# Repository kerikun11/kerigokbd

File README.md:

# KERIgoKBD (KERI's Ergonomic Keyboard)

けりの自作キーボードの設計データ。

```tree
kerigokbd/
├── hardware/
│   ├── kerigokbd/      # KERIgoKBD common PCB/case parts
│   └── README.md       # Hardware parts and compatibility table
├── software/
│   └── qmk/
│       ├── firmware/   # QMK Firmware for VIA (git submodule)
│       ├── keyboards/  # Keyboard entries for QMK Firmware
│       ├── qmk.sh      # build script
│       └── README.md   # build manual
├── .gitmodules
└── README.md
```

## 作品一覧

ハードウェア部品とファームウェアの対応は [`hardware/README.md`](./hardware/README.md) に記載。

| 作品                                                 | コメント                                                            |
| :--------------------------------------------------- | :------------------------------------------------------------------ |
| [KERIgoKBD v1](./hardware/kerigokbd/kerigokbd_v1/)   | はじめての自作エルゴノミックキーボード。                            |
| [KERIgoKBD v2](./hardware/kerigokbd/kerigokbd_v2/)   | KERIgoKBD v1 にトラックパッドを追加した構成。                       |
| [KERIgoKBD Corne v4](./hardware/kerigokbd_corne_v4/) | Corne V4 Chocolate のケースとファームウェアをカスタマイズしたもの。 |
| Keyball44 RP2040                                     | Keyball44 のマイコンボードを RP2040 Pro Micro に差し替えたもの。    |

## KERIgoKBD v1

[けり](https://github.com/kerikun11)のはじめての自作キーボード。

## KERIgoKBD v2

KERIgoKBD v1 の右手側にトラックパッドを追加した構成。

## KERIgoKBD Corne v4

[foostan](https://github.com/foostan)さんの[Corne V4 Chocolate](https://github.com/foostan/crkbd)のケースとファームウェアをカスタマイズしたもの。

## Keyball44 RP2040

[Yowkees](https://github.com/Yowkees)さんの[Keyball44](https://github.com/Yowkees/keyball)のマイコンボードを `RP2040 Pro Micro` に差し替えたもの。

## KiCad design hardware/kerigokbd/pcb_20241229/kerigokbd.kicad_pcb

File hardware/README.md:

# Hardware

KERIgoKBD のハードウェア設計データ。ここでは PCB、ケースなどの物理パーツを作品ごとに分離して管理する。

## 対応表

| 作品                                      | PCB                                         | ケース                                                          | ファームウェア                                                     | メモ                     |
| :---------------------------------------- | :------------------------------------------ | :-------------------------------------------------------------- | :----------------------------------------------------------------- | :----------------------- |
| [KERIgoKBD v1](./kerigokbd/kerigokbd_v1/) | [`pcb_20260222`](./kerigokbd/pcb_20260222/) | [`case_20260222`](./kerigokbd/case_20260222/)                   | [`kerigokbd_v1`](../software/qmk/keyboards/kerigokbd/kerigokbd_v1) | 標準構成                 |
| [KERIgoKBD v2](./kerigokbd/kerigokbd_v2/) | [`pcb_20260222`](./kerigokbd/pcb_20260222/) | [`case_20260222_trackpad`](./kerigokbd/case_20260222_trackpad/) | [`kerigokbd_v2`](../software/qmk/keyboards/kerigokbd/kerigokbd_v2) | 右手にトラックパッド追加 |

## KERIgoKBD パーツ

### PCB

| パーツ                                      | 内容                                   |
| :------------------------------------------ | :------------------------------------- |
| [`pcb_20241229`](./kerigokbd/pcb_20241229/) | v1.0 初版。I2Cピンアサインにミスあり。 |
| [`pcb_20250208`](./kerigokbd/pcb_20250208/) | v1.1 I2Cピンアサイン修正版。           |
| [`pcb_20260222`](./kerigokbd/pcb_20260222/) | v1.2 小型版。v1/v2 共通 PCB。          |

### ケース

| パーツ                                                          | 内容                                      |
| :-------------------------------------------------------------- | :---------------------------------------- |
| [`case_20250208`](./kerigokbd/case_20250208/)                   | PCB v1.0 と v1.1 向けのケース。           |
| [`case_20260222`](./kerigokbd/case_20260222/)                   | PCB v1.2 向けケース。                     |
| [`case_20260222_trackpad`](./kerigokbd/case_20260222_trackpad/) | PCB v1.2 向け、トラックパッド対応ケース。 |

## その他

- [`kerigokbd_corne_v4`](./kerigokbd_corne_v4/) は Corne V4 Chocolate のカスタムケース。

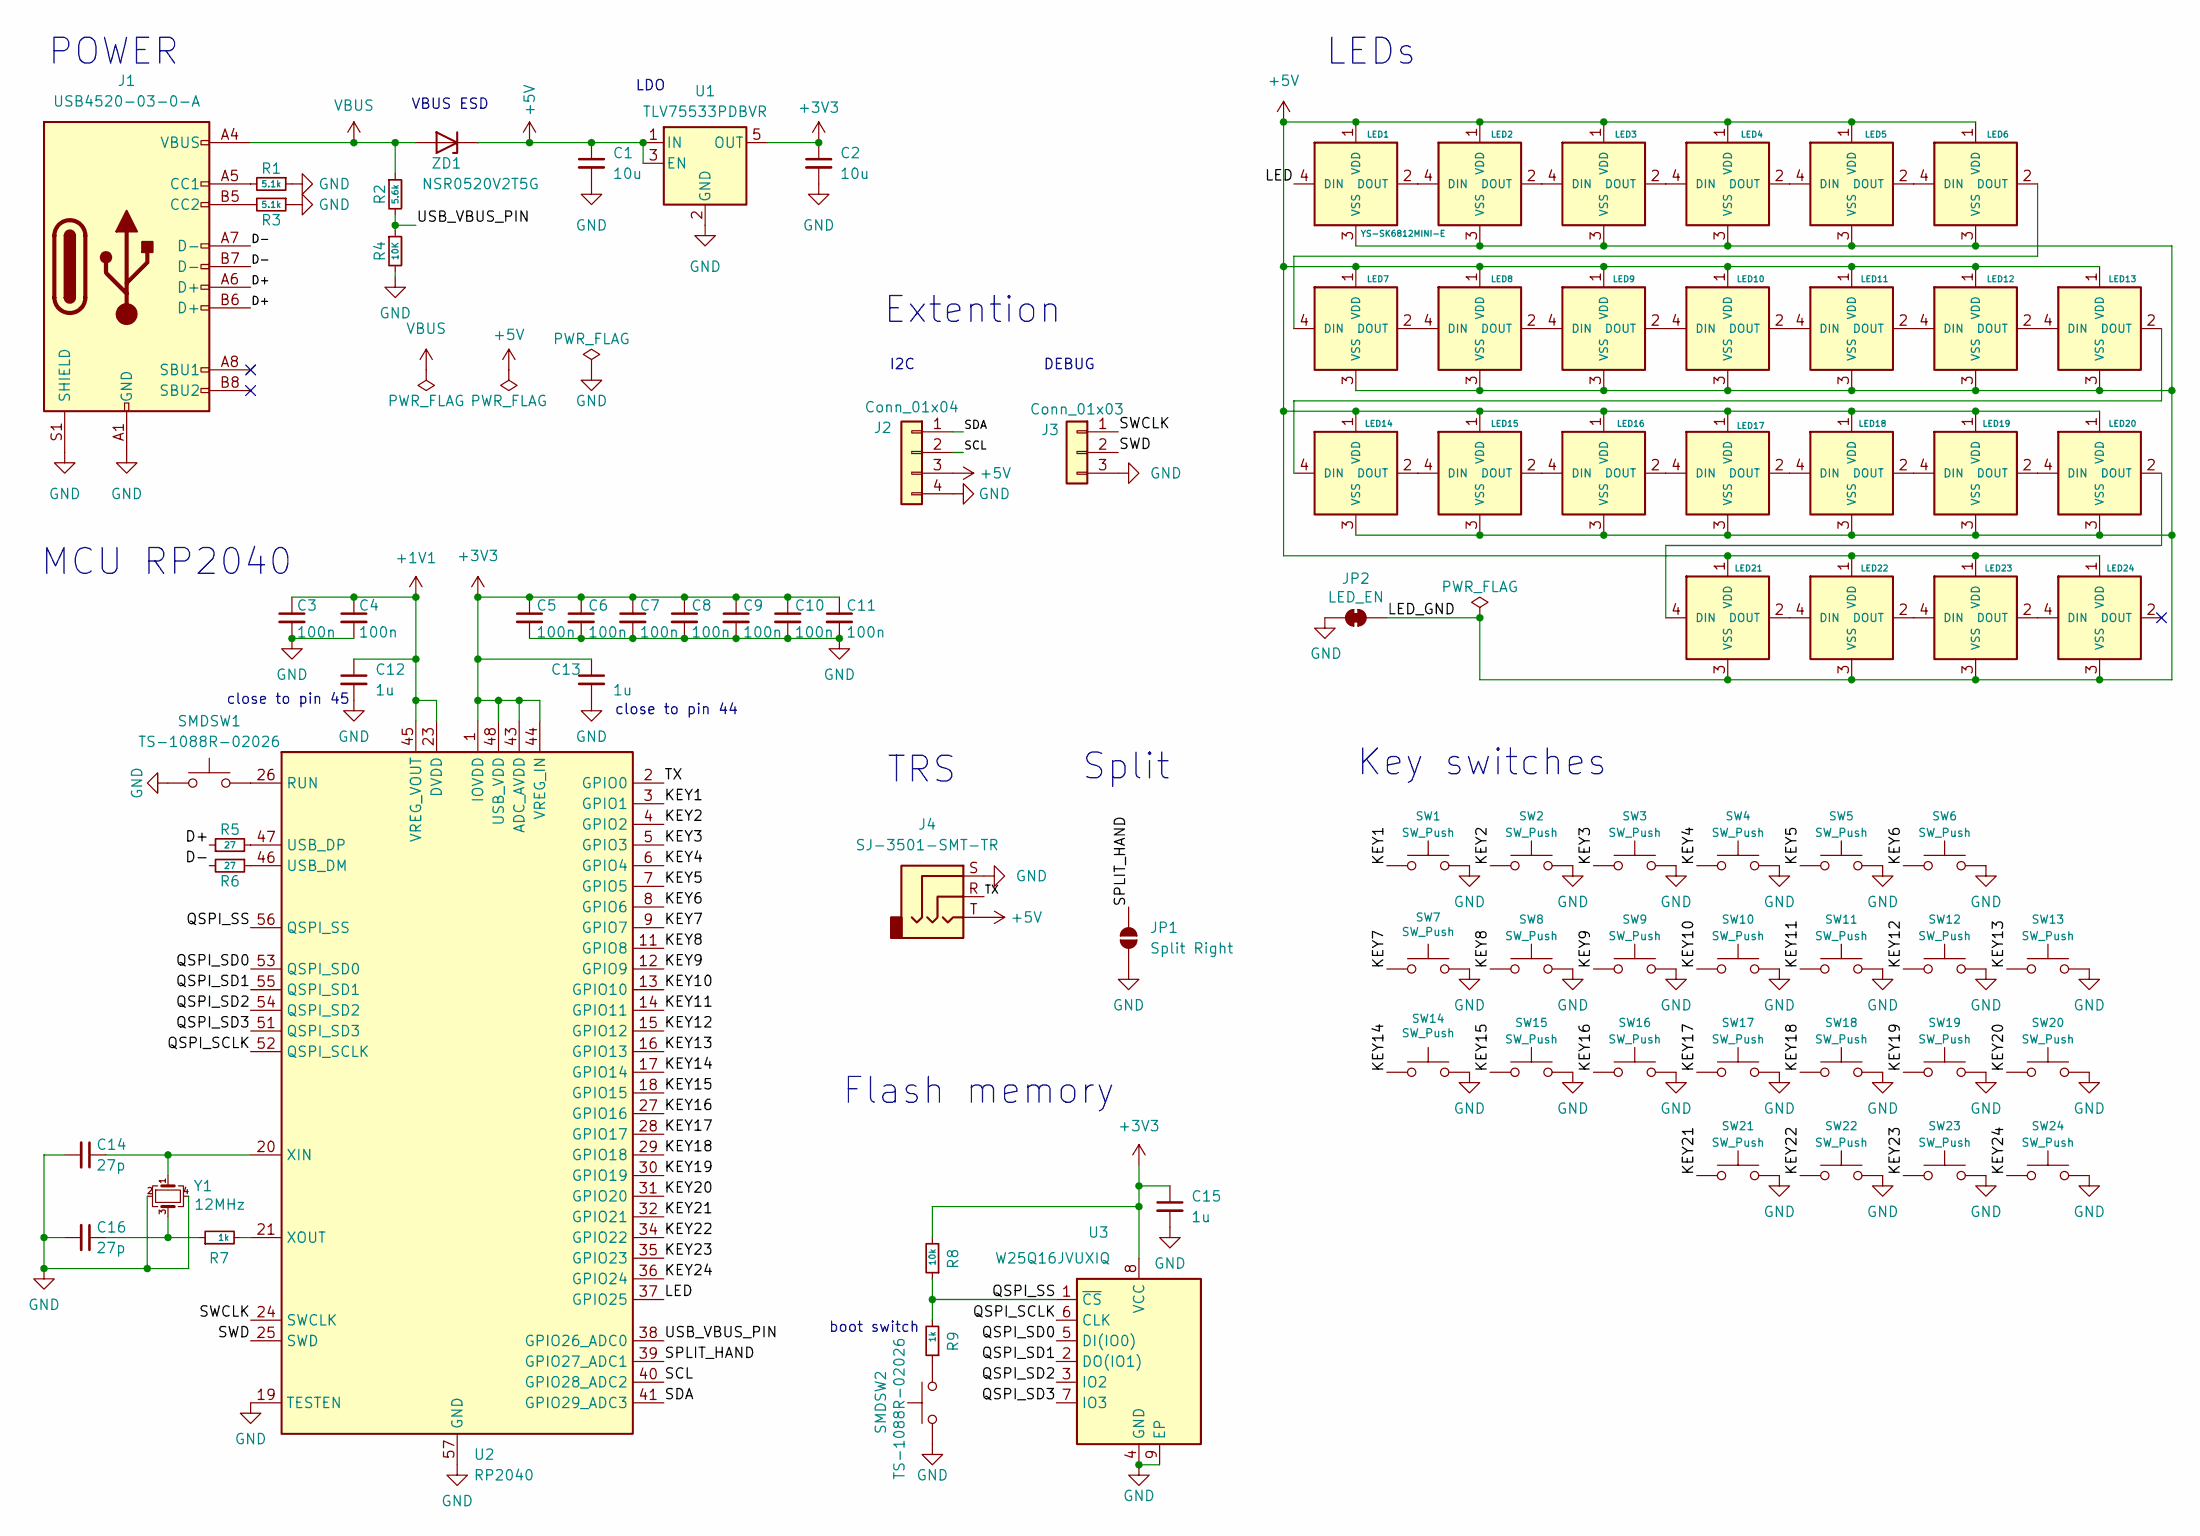
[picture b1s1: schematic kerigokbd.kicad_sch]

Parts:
C1, C2: 10u; C_0402_1005Metric
C3, C4, C5, C6, C7, C8, C9, C10, C11: 100n; C_0402_1005Metric
C12, C13, C15: 1u; C_0402_1005Metric
C14, C16: 27p; C_0402_1005Metric
J1: USB4520-03-0-A; TYPE-C-31-M-13C-dual; JLCPCB Part # C2848620
J2: Conn_01x04; PinHeader_1x04_P1.27mm_Vertical
J3: Conn_01x03; PinHeader_1x03_P1.27mm_Vertical
J4: SJ-3501-SMT-TR; PJ-398A-5A_PJ-399B-6A-dual; JLCPCB Part # C128994
JP1: Split Right; SolderJumper-2_P1.3mm_Open_TrianglePad1.0x1.5mm
JP2: LED_EN; SolderJumper-2_P1.3mm_Bridged_RoundedPad1.0x1.5mm
LED1, LED2, LED3, LED4, LED5, LED6, LED7, LED8, LED9, LED10, LED11, LED12, LED13, LED14, LED15, LED16, LED17, LED18, LED19, LED20, LED21, LED22, LED23, LED24: YS-SK6812MINI-E; YS-SK6812MINI-E-dual
R1, R3: 5.1k; R_0402_1005Metric
R2: 5.6k; R_0402_1005Metric
R4: 10K; R_0402_1005Metric
R5, R6: 27; R_0402_1005Metric
R7, R9: 1k; R_0402_1005Metric
R8: 10k; R_0402_1005Metric
SMDSW1, SMDSW2: TS-1088R-02026; PinHeader_1x02_P1.27mm_Vertical; JLCPCB Part # C455280
SW1, SW2, SW3, SW4, SW5, SW6, SW7, SW8, SW9, SW10, SW11, SW12, SW13, SW14, SW15, SW16, SW17, SW18, SW19, SW20, SW21, SW22, SW23, SW24: SW_Push; keyswitch_choc12_hotswap_1u_dual
U1: TLV75533PDBVR; SOT-23-5
U2: RP2040; QFN-56-1EP_7x7mm_P0.4mm_EP3.2x3.2mm; JLCPCB Part # C2040
U3: W25Q16JVUXIQ; Winbond_USON-8-1EP_3x2mm_P0.5mm_EP0.2x1.6mm; JLCPCB Part # C113767
Y1: 12MHz; Crystal_SMD_3225-4Pin_3.2x2.5mm; MFR.Part # Q22FA23V0041800; JLCPCB Part # C91749
ZD1: NSR0520V2T5G; D_SOD-523; JLCPCB Part # C145179

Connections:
+1V1: C3.1, C4.1, C12.1, U2.23 (DVDD), U2.45 (VREG_VOUT), U2.50 (DVDD)
+3V3: C2.1, C5.1, C6.1, C7.1, C8.1, C9.1, C10.1, C11.1, C13.1, C15.1, R8.2, U1.5 (OUT), U2.1 (IOVDD), U2.10 (IOVDD), U2.22 (IOVDD), U2.33 (IOVDD), U2.42 (IOVDD), U2.43 (ADC_AVDD), U2.44 (VREG_IN), U2.48 (USB_VDD), U2.49 (IOVDD), U3.8 (VCC)
+5V: C1.1, J2.3, J4.T, LED1.1 (VDD), LED2.1 (VDD), LED3.1 (VDD), LED4.1 (VDD), LED5.1 (VDD), LED6.1 (VDD), LED7.1 (VDD), LED8.1 (VDD), LED9.1 (VDD), LED10.1 (VDD), LED11.1 (VDD), LED12.1 (VDD), LED13.1 (VDD), LED14.1 (VDD), LED15.1 (VDD), LED16.1 (VDD), LED17.1 (VDD), LED18.1 (VDD), LED19.1 (VDD), LED20.1 (VDD), LED21.1 (VDD), LED22.1 (VDD), LED23.1 (VDD), LED24.1 (VDD), U1.1 (IN), U1.3 (EN), ZD1.1 (K)
/D+: J1.A6 (D+), J1.B6 (D+), R5.1
/D-: J1.A7 (D-), J1.B7 (D-), R6.2
/KEY1: SW1.1, U2.3 (GPIO1)
/KEY2: SW2.1, U2.4 (GPIO2)
/KEY3: SW3.1, U2.5 (GPIO3)
/KEY4: SW4.1, U2.6 (GPIO4)
/KEY5: SW5.1, U2.7 (GPIO5)
/KEY6: SW6.1, U2.8 (GPIO6)
/KEY7: SW7.1, U2.9 (GPIO7)
/KEY8: SW8.1, U2.11 (GPIO8)
/KEY9: SW9.1, U2.12 (GPIO9)
/KEY10: SW10.1, U2.13 (GPIO10)
/KEY11: SW11.1, U2.14 (GPIO11)
/KEY12: SW12.1, U2.15 (GPIO12)
/KEY13: SW13.1, U2.16 (GPIO13)
/KEY14: SW14.1, U2.17 (GPIO14)
/KEY15: SW15.1, U2.18 (GPIO15)
/KEY16: SW16.1, U2.27 (GPIO16)
/KEY17: SW17.1, U2.28 (GPIO17)
/KEY18: SW18.1, U2.29 (GPIO18)
/KEY19: SW19.1, U2.30 (GPIO19)
/KEY20: SW20.1, U2.31 (GPIO20)
/KEY21: SW21.1, U2.32 (GPIO21)
/KEY22: SW22.1, U2.34 (GPIO22)
/KEY23: SW23.1, U2.35 (GPIO23)
/KEY24: SW24.1, U2.36 (GPIO24)
/LED: LED1.4 (DIN), U2.37 (GPIO25)
/LED_GND: JP2.2 (B), LED1.3 (VSS), LED2.3 (VSS), LED3.3 (VSS), LED4.3 (VSS), LED5.3 (VSS), LED6.3 (VSS), LED7.3 (VSS), LED8.3 (VSS), LED9.3 (VSS), LED10.3 (VSS), LED11.3 (VSS), LED12.3 (VSS), LED13.3 (VSS), LED14.3 (VSS), LED15.3 (VSS), LED16.3 (VSS), LED17.3 (VSS), LED18.3 (VSS), LED19.3 (VSS), LED20.3 (VSS), LED21.3 (VSS), LED22.3 (VSS), LED23.3 (VSS), LED24.3 (VSS)
/QSPI_SCLK: U2.52 (QSPI_SCLK), U3.6 (CLK)
/QSPI_SD0: U2.53 (QSPI_SD0), U3.5 (DI(IO0))
/QSPI_SD1: U2.55 (QSPI_SD1), U3.2 (DO(IO1))
/QSPI_SD2: U2.54 (QSPI_SD2), U3.3 (IO2)
/QSPI_SD3: U2.51 (QSPI_SD3), U3.7 (IO3)
/QSPI_SS: R8.1, R9.2, U2.56 (QSPI_SS), U3.1 (~CS)
/SCL: J2.2, U2.40 (GPIO28_ADC2)
/SDA: J2.1, U2.41 (GPIO29_ADC3)
/SPLIT_HAND: JP1.2 (B), U2.39 (GPIO27_ADC1)
/SWCLK: J3.1, U2.24 (SWCLK)
/SWD: J3.2, U2.25 (SWD)
/TX: J4.R, U2.2 (GPIO0)
/USB_VBUS_PIN: R2.2, R4.1, U2.38 (GPIO26_ADC0)
GND: C1.2, C2.2, C3.2, C4.2, C5.2, C6.2, C7.2, C8.2, C9.2, C10.2, C11.2, C12.2, C13.2, C14.2, C15.2, C16.2, J1.A1 (GND), J1.A12 (GND), J1.B1 (GND), J1.B12 (GND), J1.S1 (SHIELD), J2.4, J3.3, J4.S, JP1.1 (A), JP2.1 (A), R1.1, R3.1, R4.2, SMDSW1.1, SMDSW2.1, SW1.2, SW2.2, SW3.2, SW4.2, SW5.2, SW6.2, SW7.2, SW8.2, SW9.2, SW10.2, SW11.2, SW12.2, SW13.2, SW14.2, SW15.2, SW16.2, SW17.2, SW18.2, SW19.2, SW20.2, SW21.2, SW22.2, SW23.2, SW24.2, U1.2 (GND), U2.19 (TESTEN), U2.57 (GND), U3.4 (GND), U3.9 (EP), Y1.2, Y1.4
unnamed: C16.1, R7.1, Y1.3
unnamed: J1.A5 (CC1), R1.2
unnamed: J1.B5 (CC2), R3.2
unnamed: LED1.2 (DOUT), LED2.4 (DIN)
unnamed: LED2.2 (DOUT), LED3.4 (DIN)
unnamed: LED3.2 (DOUT), LED4.4 (DIN)
unnamed: LED4.2 (DOUT), LED5.4 (DIN)
unnamed: LED5.2 (DOUT), LED6.4 (DIN)
unnamed: LED6.2 (DOUT), LED7.4 (DIN)
unnamed: LED7.2 (DOUT), LED8.4 (DIN)
unnamed: LED8.2 (DOUT), LED9.4 (DIN)
unnamed: LED9.2 (DOUT), LED10.4 (DIN)
unnamed: LED10.2 (DOUT), LED11.4 (DIN)
unnamed: LED11.2 (DOUT), LED12.4 (DIN)
unnamed: LED12.2 (DOUT), LED13.4 (DIN)
unnamed: LED13.2 (DOUT), LED14.4 (DIN)
unnamed: LED14.2 (DOUT), LED15.4 (DIN)
unnamed: LED15.2 (DOUT), LED16.4 (DIN)
unnamed: LED16.2 (DOUT), LED17.4 (DIN)
unnamed: LED17.2 (DOUT), LED18.4 (DIN)
unnamed: LED18.2 (DOUT), LED19.4 (DIN)
unnamed: LED19.2 (DOUT), LED20.4 (DIN)
unnamed: LED20.2 (DOUT), LED21.4 (DIN)
unnamed: LED21.2 (DOUT), LED22.4 (DIN)
unnamed: LED22.2 (DOUT), LED23.4 (DIN)
unnamed: LED23.2 (DOUT), LED24.4 (DIN)
unnamed: R9.1, SMDSW2.2
unnamed: SMDSW1.2, U2.26 (RUN)
unnamed: R6.1, U2.46 (USB_DM)
unnamed: R5.2, U2.47 (USB_DP)
unnamed: C14.1, U2.20 (XIN), Y1.1
unnamed: R7.2, U2.21 (XOUT)
VBUS: J1.A4 (VBUS), J1.A9 (VBUS), J1.B4 (VBUS), J1.B9 (VBUS), R2.1, ZD1.2 (A)

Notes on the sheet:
Key switches
Extention
LDO
POWER
close to pin 45
Split
VBUS ESD
I2C
boot switch
TRS
LEDs
close to pin 44
Flash memory
MCU RP2040
DEBUG

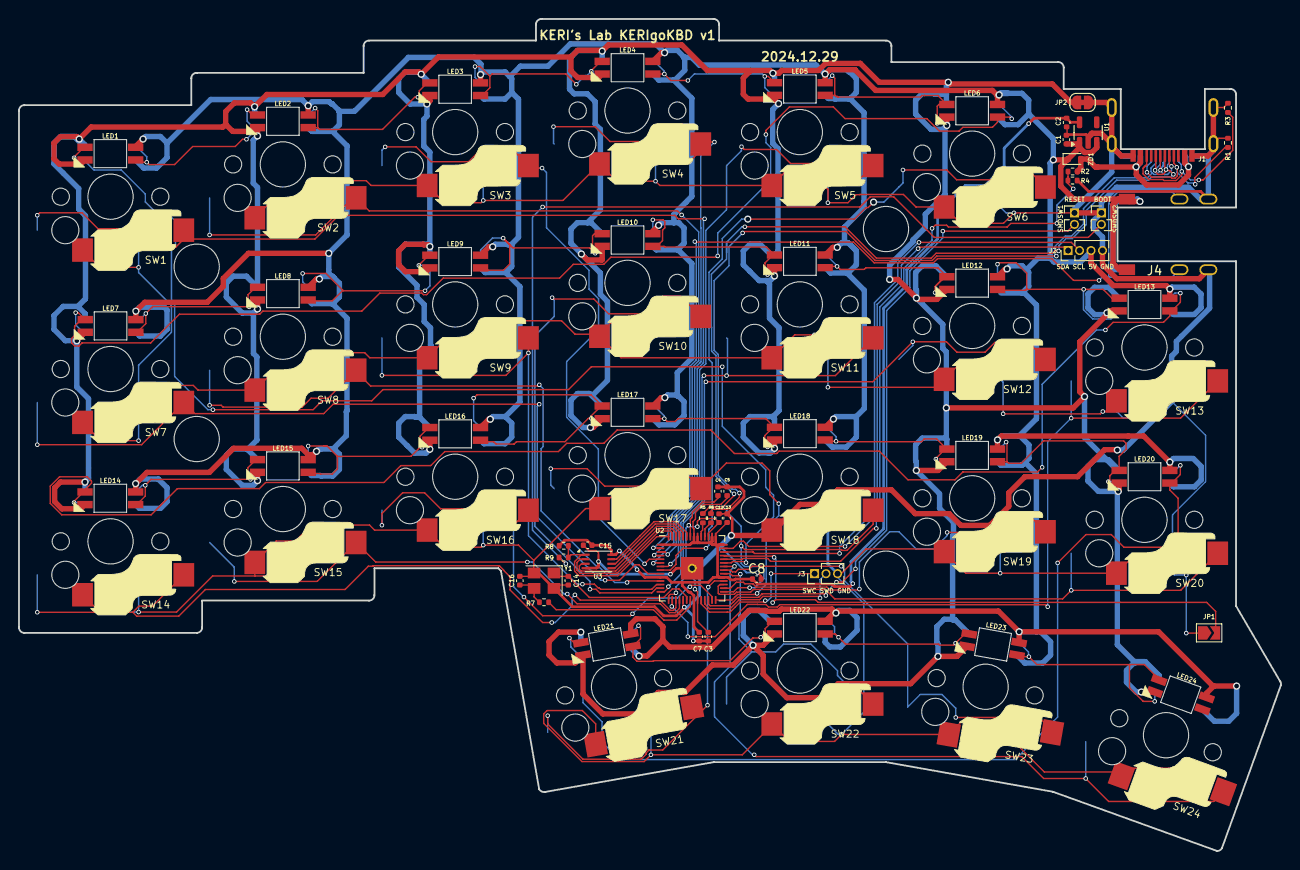
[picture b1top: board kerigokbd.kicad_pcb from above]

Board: 2 copper layers, 139.5 x 92.0 mm, 82 parts (0 on the bottom side), 78 nets.

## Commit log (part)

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2024-12-07 initial commit (empty)
2024-12-07 add readme
2024-12-07 add qmk_firmware submodule
2024-12-07 add keyboard template
2024-12-07 add src based on crkbd
2024-12-07 update structure
2024-12-07 update docs
2024-12-07 change keyboard name
2024-12-07 update keyboard info
2024-12-07 add encoder
2024-12-07 ignore .vscode
2024-12-07 add zkhk and eisu
2024-12-07 update QMK Firmware
2024-12-10 update keymap
2024-12-12 fix dynamic keycode issue
2024-12-12 update LED brightness
2024-12-15 clean src
2024-12-21 add LICENSE
2024-12-26 update rgb matrix
2024-12-26 add support for vial
2024-12-26 add keyboard images
2024-12-26 add submodule
2024-12-26 change qmk directory
2024-12-26 update script
2024-12-26 add mouse keys
2024-12-27 add pcb
2024-12-27 update pcb
2024-12-30 mv pcb
2024-12-30 add case draft
2024-12-30 update keyboard.json for new keyboard
2024-12-30 update case model
2024-12-30 update settings
2024-12-30 update case
2024-12-30 update dir structure
2024-12-30 add corne v4 firmware
2024-12-30 update scripts
2024-12-30 clean files
2024-12-30 update json
2024-12-30 add rules.mk
2024-12-31 update vial dir structure
2024-12-31 add keyball44 firmware
2024-12-31 add keyboards dir
2024-12-31 update keymaps
2025-01-01 add keyballrp
2025-01-01 update keyballrp
2025-01-01 add support for RGB Matrix and Split
2025-01-01 add keyfunc effect
2025-01-01 add via.json for keyball44rp
2025-01-01 add support for drag mode
2025-01-02 update header
2025-01-03 add kicad-kbd submodule
2025-01-03 rename kicad kbd
2025-01-03 update kicad 3d path
2025-01-03 update KERIgoKBD v1 case
2025-01-11 fix keymap
2025-01-11 update copyright
2025-01-11 update sketch pdf
2025-01-11 update headers
2025-01-11 update copyright and add via keymaps
2025-01-16 add hardware readme
2025-01-17 update sketch
2025-01-18 update license
2025-01-18 update docs and images
2025-01-18 fix image path
2025-01-18 add case of corne v4
2025-01-23 add fusion model of case
2025-01-23 add trackpad test firmware
2025-01-24 add support for trackpad
2025-01-26 update pointing code
2025-02-02 change serial pin from 0 to 29
2025-02-02 add examples dir
2025-02-17 update readme and images
2025-02-17 support multiple pcb versions
2025-02-17 update qmk
2025-03-24 add support for trackpad cirque
2025-04-11 update mouse layer
2025-04-11 update qmk_firmware
2025-04-11 fix pin assign
2025-04-11 update config
2025-05-07 disable pointing_device
2025-05-07 fix script
2025-06-15 update case models
2025-07-22 update gitignore
2025-07-23 add support for compile_commands.json
2025-07-23 clean files (delete KG_WIN_1)
2025-07-24 add readme for example
2025-10-20 add 7th layer
2025-10-27 update keymap to add tenkey
2026-02-03 Layout v2026.02.03a
2026-02-06 Layout v2026.02.06a
2026-02-20 update corne v4 layout
2026-02-27 update svg and pdf
2026-03-08 Layout v2026.03.08a
2026-03-08 Layout v2026.03.08b
2026-03-09 fix keyball44rp
2026-03-22 update keyball44rp
2026-04-04 update links
2026-04-04 mv qmk_firmware dir
2026-04-04 add qmk dir
2026-04-04 promote pcb_20250208 to main
2026-04-04 fix readme
2026-04-04 update device version
2026-04-06 fix keyboard.json
2026-04-06 Archive KERIgoKBD v1 hardware revisions
2026-04-07 mv .clang-format
2026-04-13 add pcb_20260222_trackpad
2026-04-13 add layer enum
2026-04-13 update trackpad impl
2026-04-17 update trackpad gesture
2026-04-17 fix trackpad behavior
2026-04-18 fix split trackpad
2026-04-18 update rgb_matrix_user
2026-04-18 fix trackpad
2026-04-18 update trackpad
2026-04-19 add activity sync
2026-04-19 add build workflow
2026-04-19 fix workflow
2026-04-19 update workflow
2026-04-21 update via.json for KERIgoKBD v1
2026-04-27 refactor repository structure
2026-04-27 update firmware
2026-04-27 add support for zoom mode
2026-04-28 update kerigokbd v2 config
2026-05-02 update auto mouse layer timeout
2026-05-23 update timing parameter
2026-06-27 update mouse keycode
